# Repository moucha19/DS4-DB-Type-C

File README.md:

# USB-C daughterboard for DualShock 4 controller

## Features 

* Almost drop-in replacement **for JDS-040**
    + Original dimensions are maintained
    + Screw hole is in the right spot
    + However, you still need to enlarge the connector hole in the controller case - obviously
* Compatible with USB-C to USB-C cables
* Board schematic is as close as possible to the original
* All components can be purchased from [LCSC](https://www.lcsc.com/)

## Manufacturing instructions

You can find the archive with Gerber files in the releases section. 

**When ordering, you must choose a 1.2 mm PCB thickness!**

### Bill of Materials

| Designator | Footprint                                                 | LCSC    |
|------------|-----------------------------------------------------------|---------|
| C1         | 10nF  SMD 0402 Capacitor | [C15195](https://www.lcsc.com/product-detail/C15195.html)  |
| D1         | LED RGB Foshan FM-3510RGBA-SG           | [C727903](https://www.lcsc.com/product-detail/C727903.html) |
| F1         | 6V 750mA SMD 0603 Fuse       | [C207016](https://www.lcsc.com/product-detail/C207016.html) |
| FL1        | TDK MCZ1210DH Common mode filter              | [C383353](https://www.lcsc.com/product-detail/C383353.html) |
| J1         | USB-C Receptacle GT-USB-7025             | [C963213](https://www.lcsc.com/product-detail/C963213.html) |
| J2         | JUSHUO AFC42-S12FMA-1H or MOLEX 5034801200 | [C466532](https://www.lcsc.com/product-detail/C466532.html) or [C587969](https://www.lcsc.com/product-detail/C587969.html) |
| R1,R2      | 5.1k  SMD 0402 Resistor  | [C105872](https://www.lcsc.com/product-detail/C105872.html) |

## PCB Assembly

This is a very small and finicky board. I made no optimizations for the SMT assembly, because you need to solder fine pitch connectors and components on both sides of the board. It may still be a viable option if you can get assembly for both sides, but since the part count is very low, you can also manage the assembly on your own if you have a right equipment. 

Hot air gun is very handy, especially for soldering of the USB-C and FPC connectors. In my opinion, the easiest method is to tin all of the pads first and then simply position the connectors under the hot air. Rest of the components is manageable with a reasonably fine soldering iron.

## Mounting instructions

I would highly recommend you to watch instruction video from Marius Heier, on [YouTube](https://www.youtube.com/watch?v=nGKyBJVDXDQ). He created it as a guide for mounting of his own USB-C DualShock 4 mods and his advice on how to enlarge the charging port hole is excellent. Definitely start from the inside first. It might be tempting to grab a Dremel but it's safer to proceed just like in the video, manually with a small file. 

Some additional advice that I can give after going through the process is to take it slow once you start making the charging port hole larger. You absolutely **MUST** take away some material both from top and bottom of the hole. One mistake I did was that I focused on the bottom first and then went a little overboard. I should've proceeded symmetricaly because the top also had to be filed down. You can find detailed photos below so you have some idea where roughly to stop. The USB symbol is a good reference.

The toughest challenge when designing the board was deciding where exactly to position the charging port. I did not want it to protrude but on the other hand, I did not want to bury it too much, with a visible gap between the plastic and the edge of the connector. In the end, this is how it looks and I'm quite satisfied with the result. The bottom of the connector is visible a little bit, but the top edge is in the ideal position. Anyways, here is a detail so you easily decide to modify the board and shift the connector in either direction based on your preference. The protrusion is roughly **0.4 mm**.

Rest of the process is very easy though and the board should fit snugly. When it comes to the light output, the LED I chose performs as well as the original and I was not able to tell the difference.

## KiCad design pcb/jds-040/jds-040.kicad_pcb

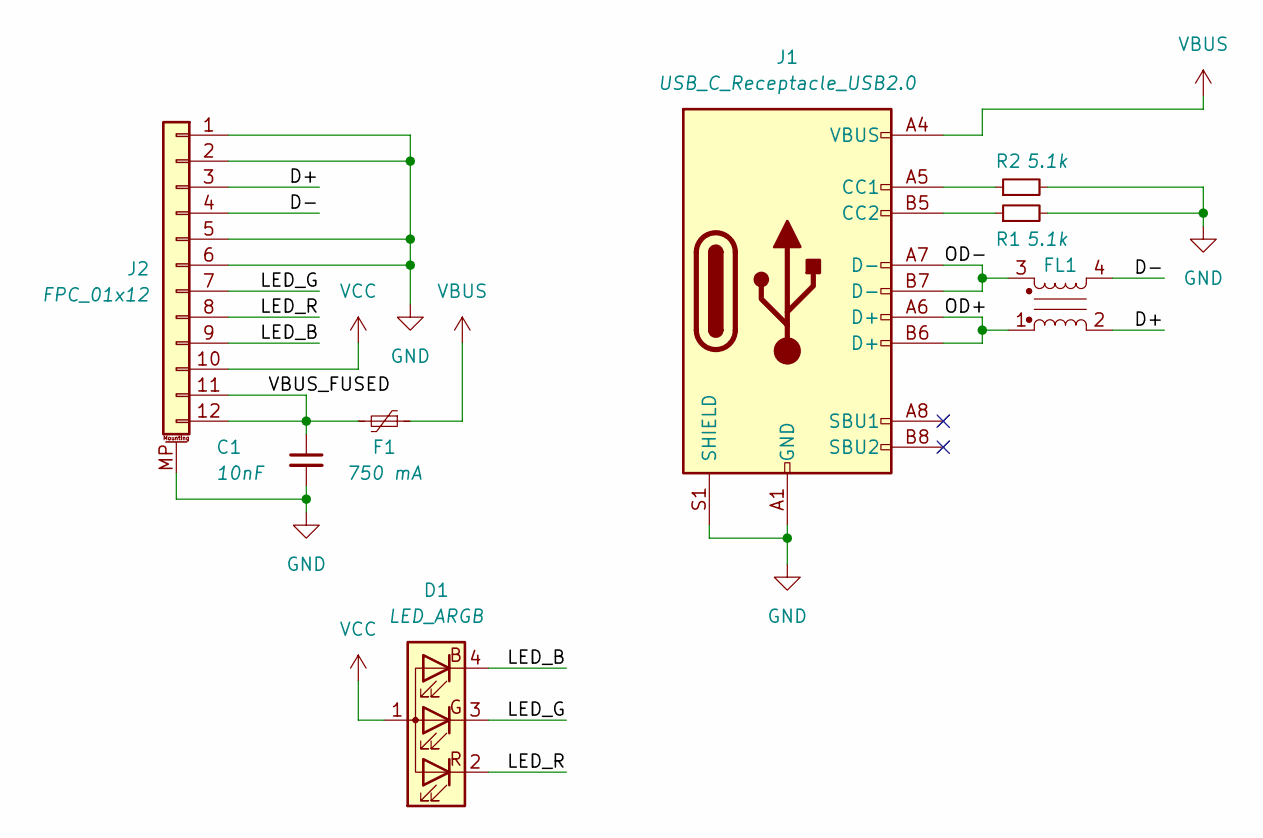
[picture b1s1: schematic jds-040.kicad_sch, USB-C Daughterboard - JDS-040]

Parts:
C1: 10nF; C_0402_1005Metric_Pad0.74x0.62mm_HandSolder; LCSC C15195
D1: LED_ARGB; LED_RGB_Foshan-FM-3510RGBA-SG; LCSC C727903
F1: 750 mA; Fuse_0603_1608Metric_Pad1.05x0.95mm_HandSolder; LCSC C207016
FL1: Filter_EMI_CommonMode; L_CommonMode_TDK_MCZ1210DH; LCSC C383353
J1: USB_C_Receptacle_USB2.0; USBC_Receptacle_GT-USB-7025; LCSC C963213
J2: FPC_01x12; FPC_CompactUniversal_12P; LCSC C466532
R1, R2: 5.1k; R_0402_1005Metric_Pad0.72x0.64mm_HandSolder; LCSC C105872

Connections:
/D+: FL1.2, J2.3
/D-: FL1.4, J2.4
/LED_B: D1.4 (BK), J2.9
/LED_G: D1.3 (GK), J2.7
/LED_R: D1.2 (RK), J2.8
/OD+: FL1.1, J1.A6 (D+), J1.B6 (D+)
/OD-: FL1.3, J1.A7 (D-), J1.B7 (D-)
/VBUS_FUSED: C1.1, F1.2, J2.11, J2.12
GND: C1.2, J1.A1 (GND), J1.A12 (GND), J1.B1 (GND), J1.B12 (GND), J1.S1 (SHIELD), J2.1, J2.2, J2.5, J2.6, J2.MP (MountPin), R1.2, R2.2
unnamed: J1.A5 (CC1), R2.1
unnamed: J1.B5 (CC2), R1.1
VBUS: F1.1, J1.A4 (VBUS), J1.A9 (VBUS), J1.B4 (VBUS), J1.B9 (VBUS)
VCC: D1.1 (A), J2.10

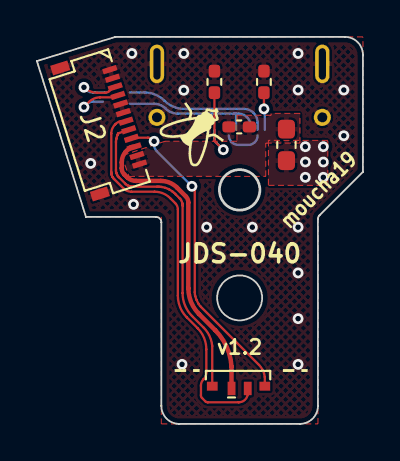
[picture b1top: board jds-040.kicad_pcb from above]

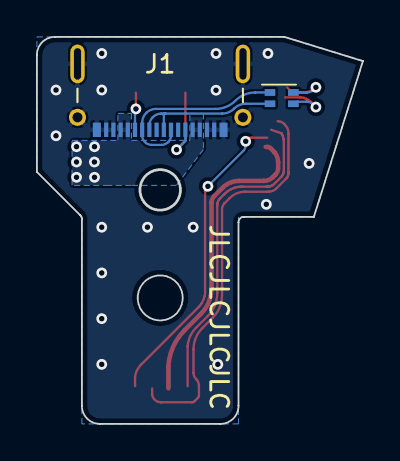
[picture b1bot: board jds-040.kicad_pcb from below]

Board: 2 copper layers, 18.1 x 21.4 mm, 8 parts (2 on the bottom side), 13 nets.

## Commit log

2023-11-30 Initial commit.
2023-11-30 Rounded all tracks, increased spaces in ground zone.
2023-11-30 Finished silkscreen, minor adjustments.
2023-12-03 Fixed DRC errors, cleaned tracks.
2024-01-10 Increased thermal relief bridge width, minor fixes.
2024-02-10 Updated sheets and component properties.
2024-02-10 Added license notice
2024-02-10 Updated .gitignore to ignore fabrication outputs
2024-02-10 Adjusted board layer stack.
2024-02-10 Added README.md and PCB image
2024-02-11 Added photos with a description of mounting process in README
2024-02-11 Connected shield to ground just like in the original part.
2024-02-11 Updated documentation
2024-04-28 Replaced fuse with a part that satisfies DS4 current rating, upgraded project to Kicad 8
2024-04-28 Updated board bicture to 1.2
2024-04-28 Changed F2,D2 to F1,D1

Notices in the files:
pcb/jds-040/jds-040.kicad_pcb:
Licensed under CERN-OHL-W v2
